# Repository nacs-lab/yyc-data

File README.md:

# License

All source code in this repo is under GPLv3+.

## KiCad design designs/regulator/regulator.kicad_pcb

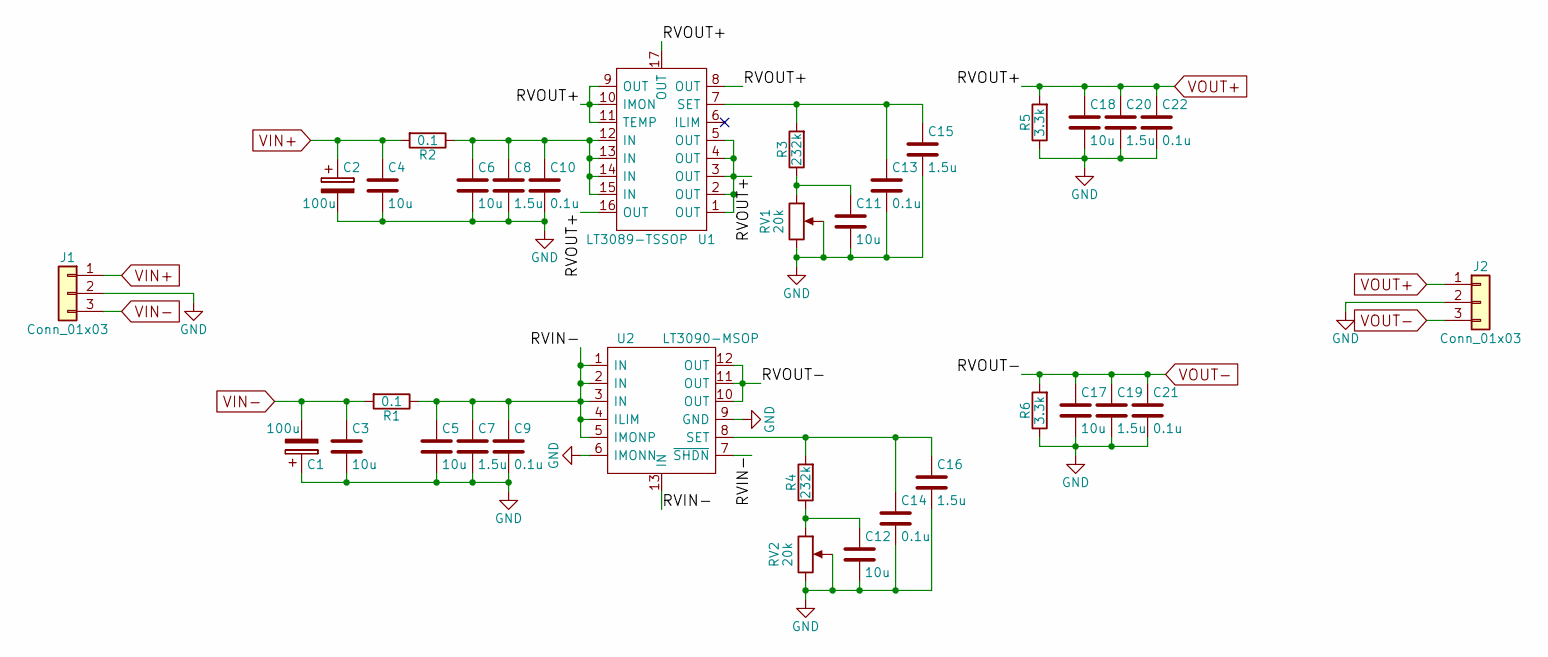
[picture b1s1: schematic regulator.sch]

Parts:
C1, C2: 100u; CP_Radial_D10.0mm_P5.00mm
C3, C4, C5, C6, C11, C12, C17, C18: 10u; C_0603
C7, C8, C15, C16, C19, C20: 1.5u; C_0805
C9, C10, C13, C14, C21, C22: 0.1u; C_0805
J1, J2: Conn_01x03; 3-pins_150mil
R1, R2: 0.1; R_0603
R3, R4: 232k; R_0603
R5, R6: 3.3k; R_0603
RV1, RV2: 20k; Potentiometer_Trimmer_Bourns_3269W
U1: LT3089-TSSOP; TSSOP-16-1EP_4.4x5mm_Pitch0.65mm
U2: LT3090-MSOP; MSOP-12-1EP_3x4mm_Pitch0.65mm

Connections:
/RVIN-: C5.1, C7.1, C9.1, R1.1, U2.1 (IN), U2.2 (IN), U2.3 (IN), U2.4 (ILIM), U2.5 (IMONP), U2.7 (~SHDN), U2.13 (IN)
GND: C1.1, C2.2, C3.2, C4.2, C5.2, C6.2, C7.2, C8.2, C9.2, C10.2, C11.2, C12.2, C13.2, C14.2, C15.2, C16.2, C17.2, C18.2, C19.2, C20.2, C21.2, C22.2, J1.2, J2.2, R5.1, R6.1, RV1.2, RV1.3, RV2.2, RV2.3, U2.6 (IMONN), U2.9 (GND)
unnamed: C6.1, C8.1, C10.1, R2.1, U1.12 (IN), U1.13 (IN), U1.14 (IN), U1.15 (IN)
unnamed: C11.1, R3.1, RV1.1
unnamed: C12.1, R4.1, RV2.1
unnamed: C13.1, C15.1, R3.2, U1.7 (SET)
unnamed: C14.1, C16.1, R4.2, U2.8 (SET)
VIN+: C2.1, C4.1, J1.1, R2.2
VIN-: C1.2, C3.1, J1.3, R1.2
VOUT+: C18.1, C20.1, C22.1, J2.1, R5.2, U1.1 (OUT), U1.2 (OUT), U1.3 (OUT), U1.4 (OUT), U1.5 (OUT), U1.8 (OUT), U1.9 (OUT), U1.10 (IMON), U1.11 (TEMP), U1.16 (OUT), U1.17 (OUT)
VOUT-: C17.1, C19.1, C21.1, J2.3, R6.2, U2.10 (OUT), U2.11 (OUT), U2.12 (OUT)

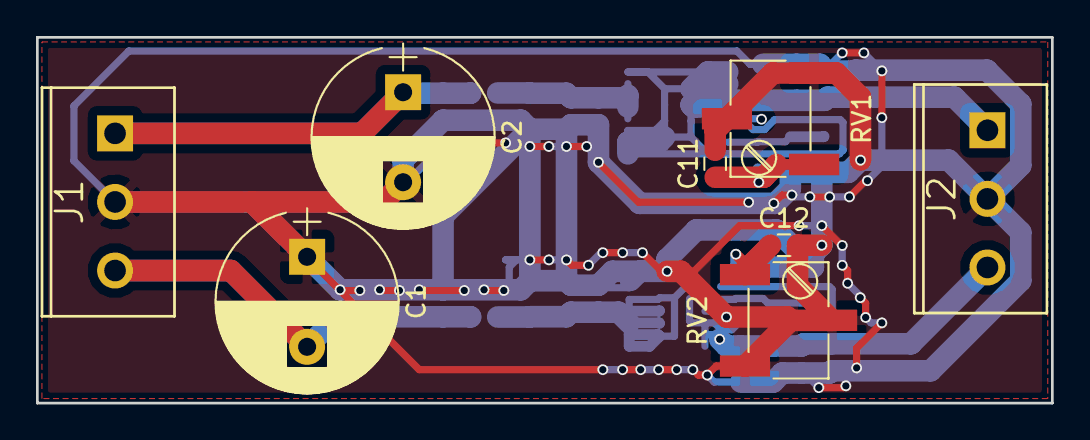
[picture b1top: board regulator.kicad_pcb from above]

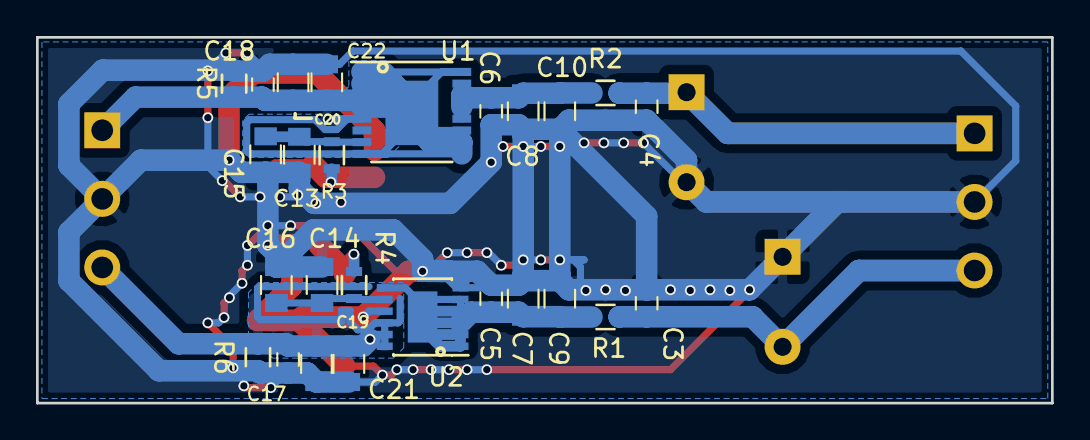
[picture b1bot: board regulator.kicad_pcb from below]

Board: 4 copper layers, 56.4 x 20.3 mm, 34 parts (26 on the bottom side), 11 nets.

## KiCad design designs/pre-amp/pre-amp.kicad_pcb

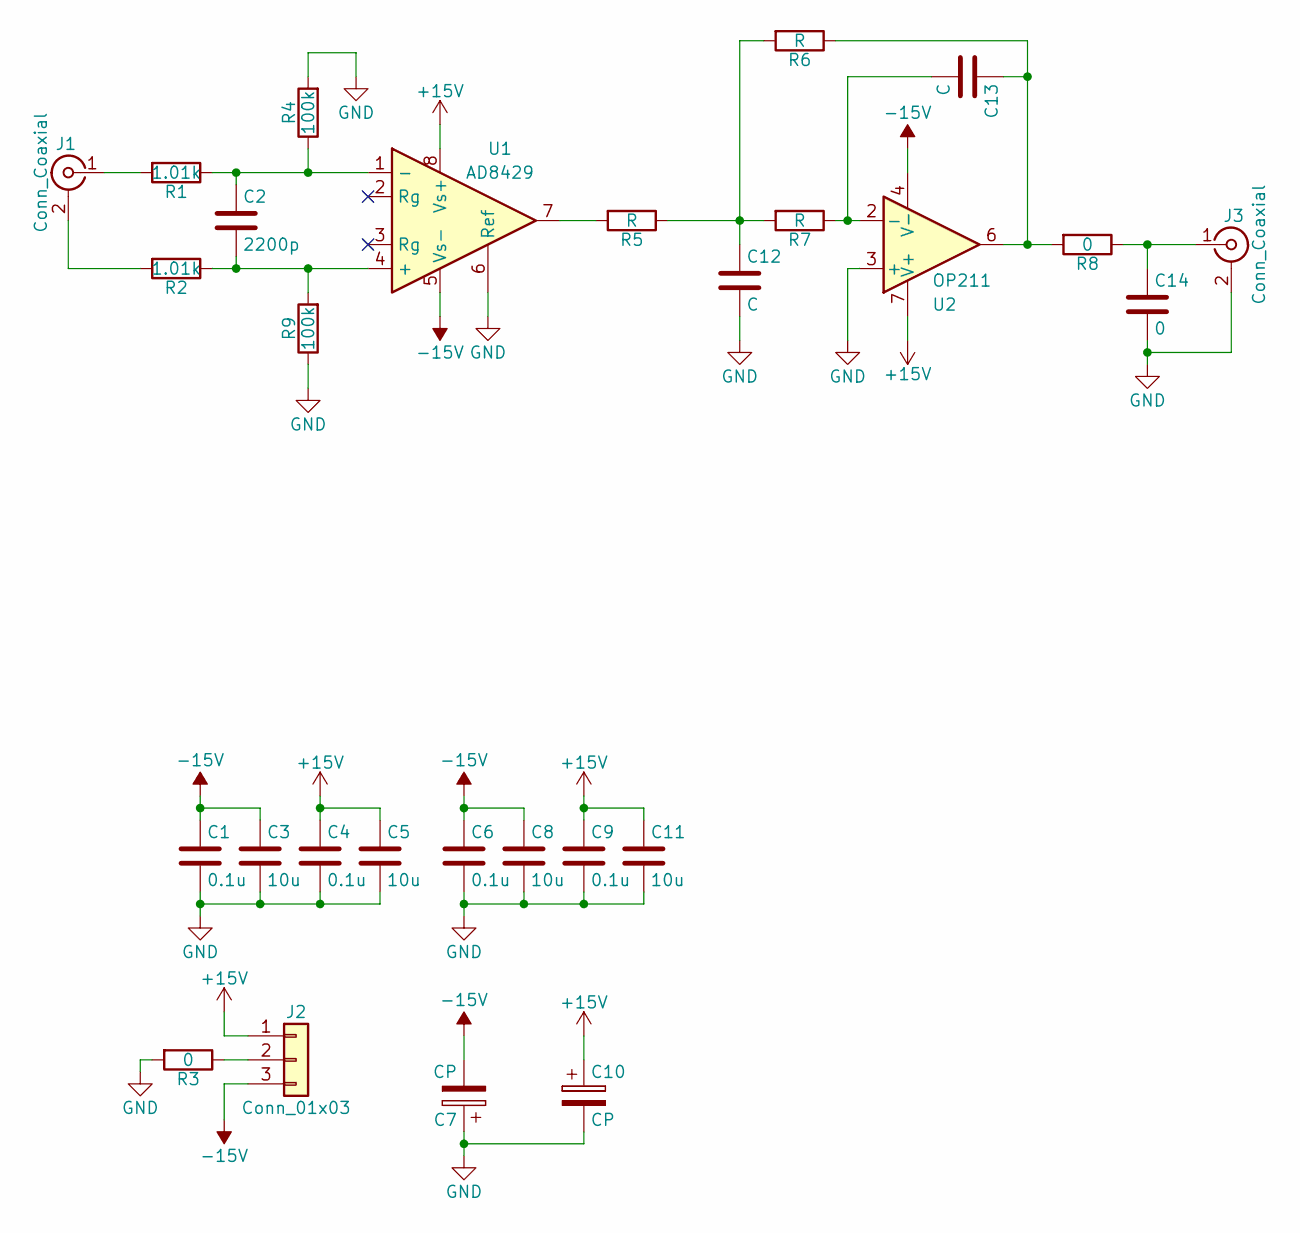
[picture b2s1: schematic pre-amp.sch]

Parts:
C1, C4, C6, C9: 0.1u; C_0603
C2: 2200p; C_0603
C3, C5, C8, C11: 10u; C_0603
C7, C10: CP; CP_Radial_D5.0mm_P2.00mm
C12, C13: C; C_0603
C14: 0; C_0603
J1, J3: Conn_Coaxial; BNC_Socket_Right-Angle_LargePads
J2: Conn_01x03; 3-pins_150mil
R1, R2: 1.01k; R_0603
R3, R8: 0; R_0603
R4, R9: 100k; R_0603
R5, R6, R7: R; R_0603
U1: AD8429; SOIC-8_3.9x4.9mm_Pitch1.27mm
U2: OP211; SOIC-8_3.9x4.9mm_Pitch1.27mm

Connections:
+15V: C4.1, C5.1, C9.1, C10.1, C11.1, J2.1, U1.8 (Vs+), U2.7 (V+)
-15V: C1.1, C3.1, C6.1, C7.2, C8.1, J2.3, U1.5 (Vs-), U2.4 (V-)
GND: C1.2, C3.2, C4.2, C5.2, C6.2, C7.1, C8.2, C9.2, C10.2, C11.2, C12.2, C14.2, J3.2 (Ext), R3.2, R4.2, R9.1, U1.6 (Ref), U2.3 (+)
unnamed: C2.1, R1.1, R4.1, U1.1 (-)
unnamed: C2.2, R2.1, R9.2, U1.4 (+)
unnamed: C12.1, R5.1, R6.2, R7.2
unnamed: C13.1, R6.1, R8.2, U2.6
unnamed: C13.2, R7.1, U2.2 (-)
unnamed: C14.1, J3.1 (In), R8.1
unnamed: J1.1 (In), R1.2
unnamed: J1.2 (Ext), R2.2
unnamed: J2.2, R3.1
unnamed: R5.2, U1.7

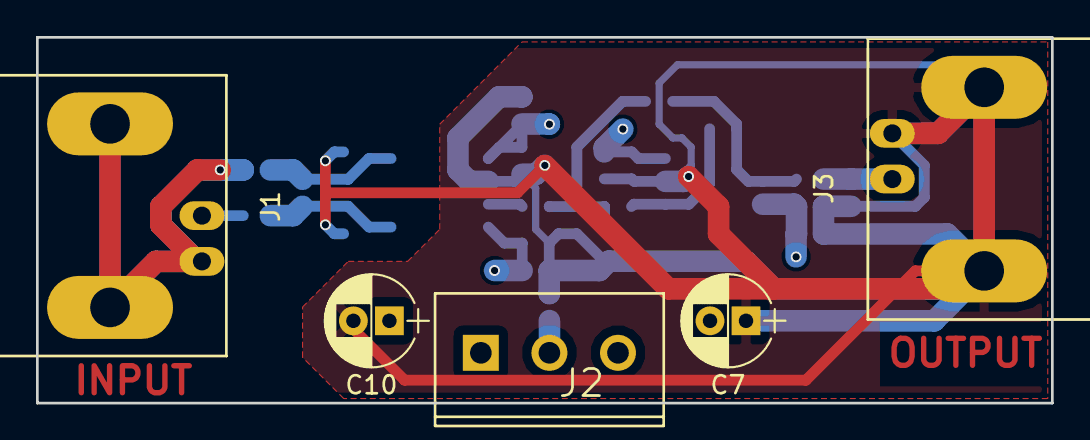
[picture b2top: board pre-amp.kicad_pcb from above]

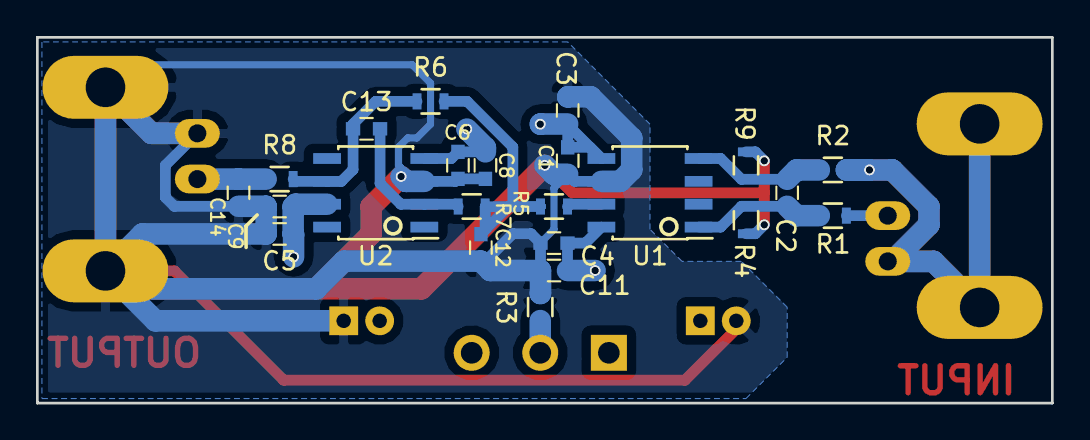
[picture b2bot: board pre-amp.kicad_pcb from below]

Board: 4 copper layers, 56.4 x 20.3 mm, 28 parts (23 on the bottom side), 13 nets.

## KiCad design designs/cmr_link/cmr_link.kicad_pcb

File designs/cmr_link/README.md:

# Orientations

Both connectors (Camera link an the 2x30 connector to the breakout board) and the
decoder chip are on the same (front) side of the board, which is the side that
is closer to the FMC connector and the DDS power supply connectors on the
breakout board. Also the side that is farther from the FPGA board/chip.

When looking from the front side of the board with the 2x30 connector on the
bottom and the camera link connector on the top, the PIN 1 of the 2x30 connector
is on the bottom left of the board and it should be connected to the ground on
the breakout board as well as all other odd number pins on this connector.
Pin 60 of the connector is VCC3V3 from the FPGA board.

# Camera link pin assignments

According to [Andor's document](http://www.andor.com/learning-academy/camera-link-output-ixon-ultra-output-for-direct-data-access), each pixel is a 16bit little endian integer, and according to the standard Port A and Port B should be used in this case.

# Microstrip

Trace width: 10 mil

Trace separation: 6 mil

Trace thickness: 1.7 mil

Dielectric thickness: 11.9 mil

Relative dielectric constant: 4.5

Differential impedance: 100.4 Ohm

# Useful documents

* Sunstone

    [Sunstone capabilities](http://www.sunstone.com/pcb-capabilities/pcb-manufacturing-capabilities)

    [Sunstone board dimensions](http://www.sunstone.com/pcb-products/pcbexpress-quickturn/quickturn-pcb-construction)

* Calculators

    [Microstrip calculator](http://www.multek.se/engelska/engineering/pcb-structures-2/differential-microstrip-impedance-calculator-2)

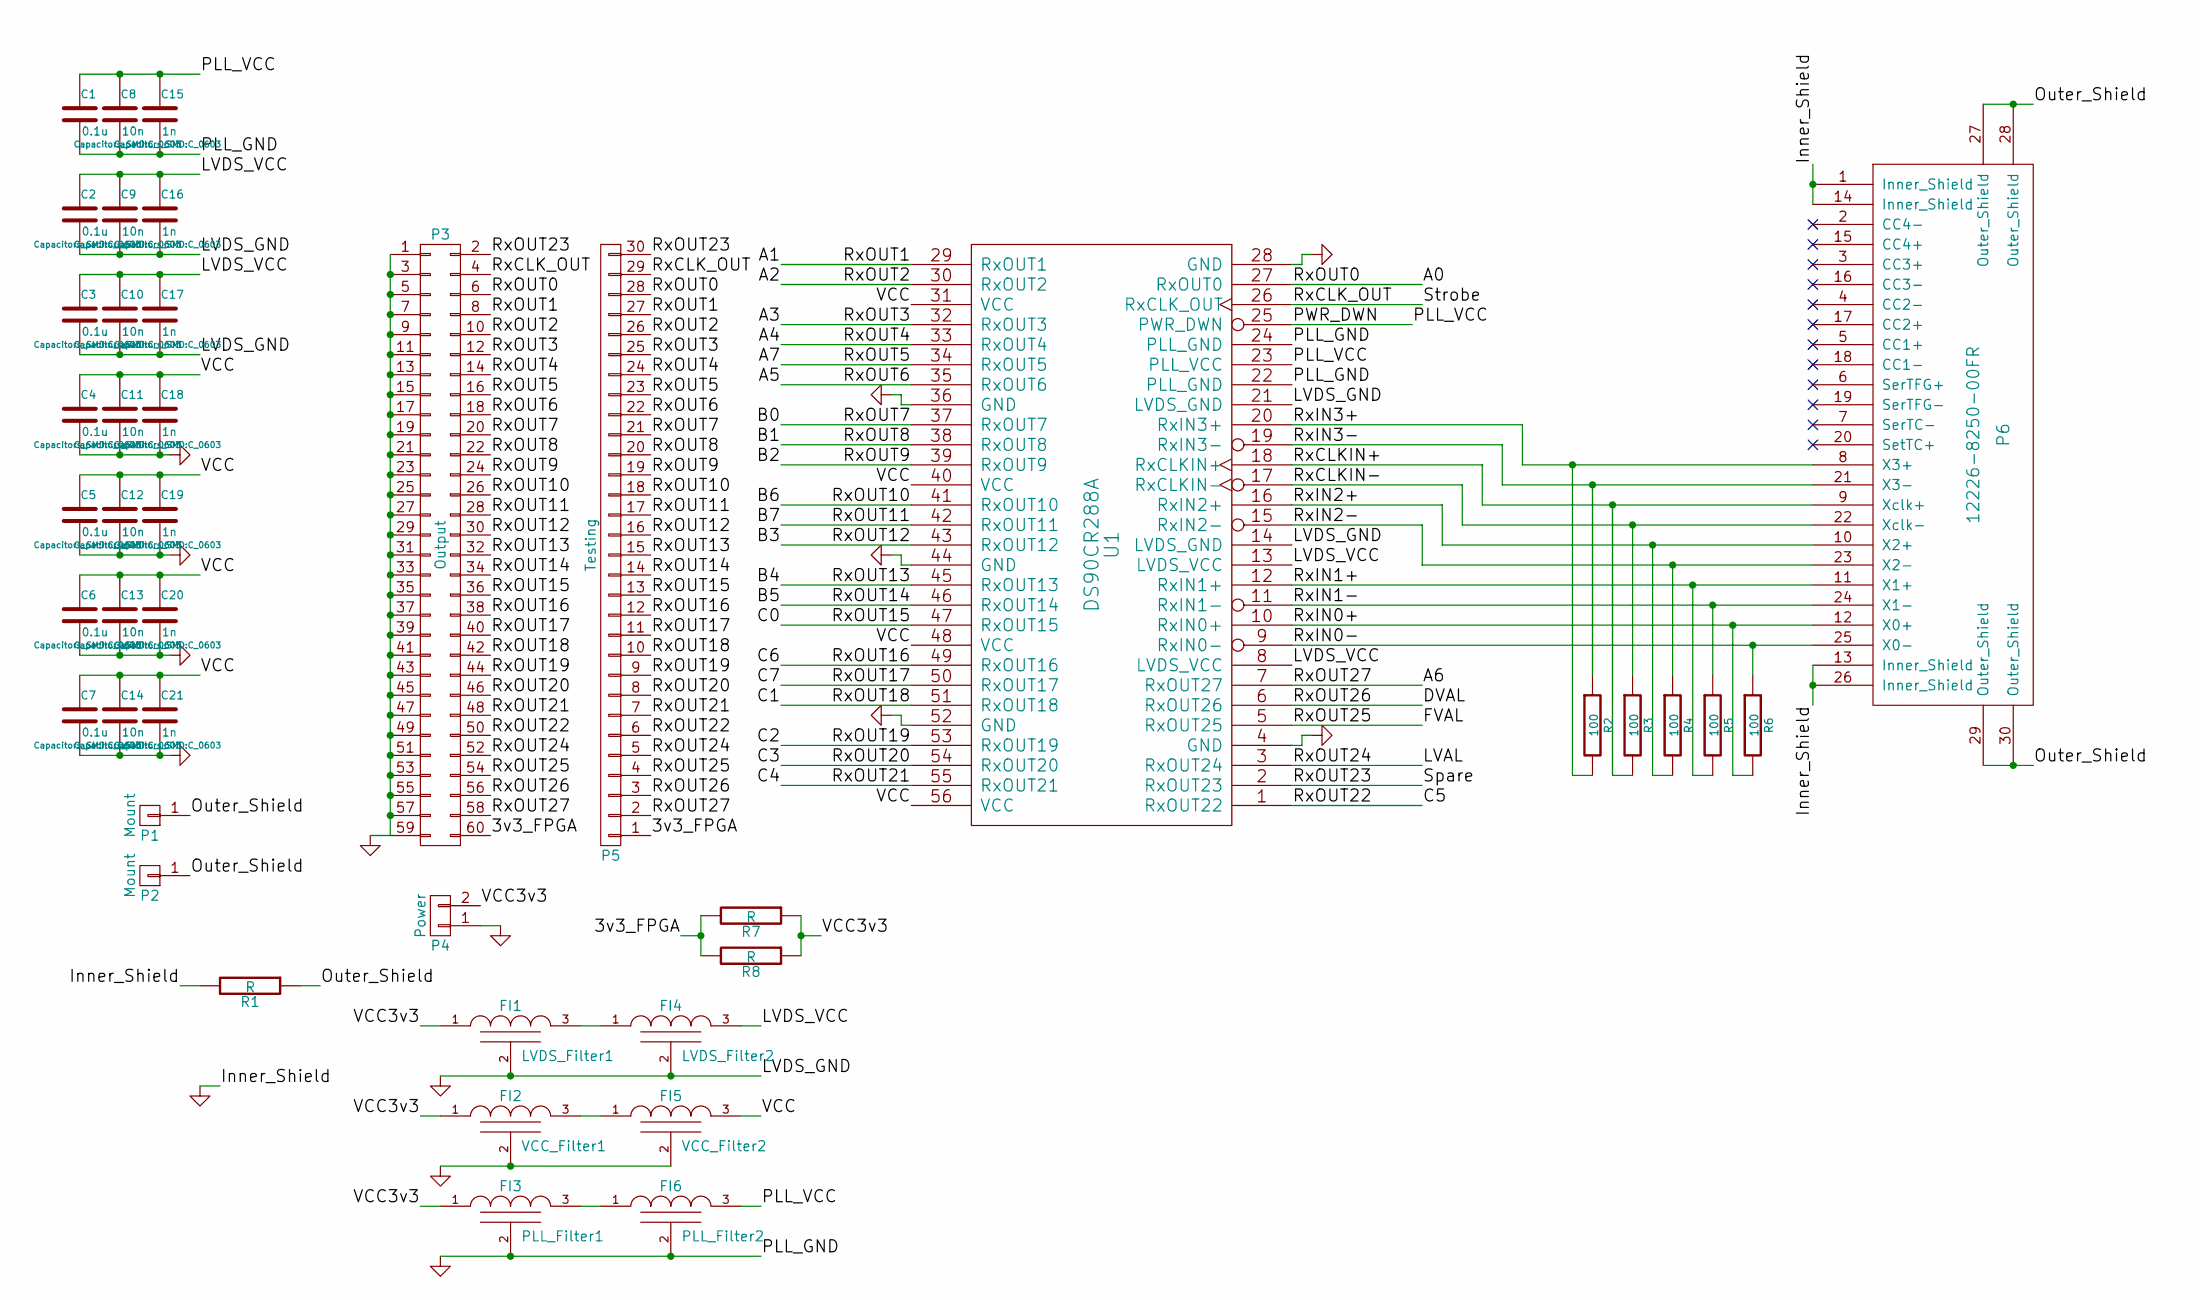
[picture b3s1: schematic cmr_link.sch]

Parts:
C1, C2, C3, C4, C5, C6, C7: 0.1u; C_0603
C8, C9, C10, C11, C12, C13, C14: 10n; C_0603
C15, C16, C17, C18, C19, C20, C21: 1n; C_0603
FI1: LVDS_Filter1; EMI_Filter_1207
FI2: VCC_Filter1; EMI_Filter_1207
FI3: PLL_Filter1; EMI_Filter_1207
FI4: LVDS_Filter2; EMI_Filter_1207
FI5: VCC_Filter2; EMI_Filter_1207
FI6: PLL_Filter2; EMI_Filter_1207
P1, P2: Mount; 1pin
P3: Output; 2x30_2mm
P4: Power; 2-pins_150mil
P5: Testing; 1x30_2mm
P6: 12226-8250-00FR
R1, R7, R8: R; R_0603
R2, R3, R4, R5, R6: 100; R_0603
U1: DS90CR288A; tssop-56-DGG

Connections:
/3v3_FPGA: P3.60, P5.1, R7.2, R8.2
/A0: P3.6, P5.28, U1.27 (RxOUT0)
/A1: P3.8, P5.27, U1.29 (RxOUT1)
/A2: P3.10, P5.26, U1.30 (RxOUT2)
/A3: P3.12, P5.25, U1.32 (RxOUT3)
/A4: P3.14, P5.24, U1.33 (RxOUT4)
/A5: P3.18, P5.22, U1.35 (RxOUT6)
/A6: P3.58, P5.2, U1.7 (RxOUT27)
/A7: P3.16, P5.23, U1.34 (RxOUT5)
/B0: P3.20, P5.21, U1.37 (RxOUT7)
/B1: P3.22, P5.20, U1.38 (RxOUT8)
/B2: P3.24, P5.19, U1.39 (RxOUT9)
/B3: P3.30, P5.16, U1.43 (RxOUT12)
/B4: P3.32, P5.15, U1.45 (RxOUT13)
/B5: P3.34, P5.14, U1.46 (RxOUT14)
/B6: P3.26, P5.18, U1.41 (RxOUT10)
/B7: P3.28, P5.17, U1.42 (RxOUT11)
/C0: P3.36, P5.13, U1.47 (RxOUT15)
/C1: P3.42, P5.10, U1.51 (RxOUT18)
/C2: P3.44, P5.9, U1.53 (RxOUT19)
/C3: P3.46, P5.8, U1.54 (RxOUT20)
/C4: P3.48, P5.7, U1.55 (RxOUT21)
/C5: P3.50, P5.6, U1.1 (RxOUT22)
/C6: P3.38, P5.12, U1.49 (RxOUT16)
/C7: P3.40, P5.11, U1.50 (RxOUT17)
/DVAL: P3.56, P5.3, U1.6 (RxOUT26)
/FVAL: P3.54, P5.4, U1.5 (RxOUT25)
/LVAL: P3.52, P5.5, U1.3 (RxOUT24)
/LVDS_VCC: C2.1, C3.1, C9.1, C10.1, C16.1, C17.1, FI4.3 (VO), U1.8 (LVDS_VCC), U1.13 (LVDS_VCC)
/Outer_Shield: P1.1, P2.1, P6.27 (Outer_Shield), P6.28 (Outer_Shield), P6.29 (Outer_Shield), P6.30 (Outer_Shield), R1.1
/PLL_VCC: C1.1, C8.1, C15.1, FI6.3 (VO), U1.23 (PLL_VCC), U1.25 (PWR_DWN)
/RxCLKIN+: P6.9 (Xclk+), R3.2, U1.18 (RxCLKIN+)
/RxCLKIN-: P6.22 (Xclk-), R3.1, U1.17 (RxCLKIN-)
/RxCLK_OUT: P3.4, P5.29, U1.26 (RxCLK_OUT)
/RxIN0+: P6.12 (X0+), R6.2, U1.10 (RxIN0+)
/RxIN0-: P6.25 (X0-), R6.1, U1.9 (RxIN0-)
/RxIN1+: P6.11 (X1+), R5.2, U1.12 (RxIN1+)
/RxIN1-: P6.24 (X1-), R5.1, U1.11 (RxIN1-)
/RxIN2+: P6.10 (X2+), R4.2, U1.16 (RxIN2+)
/RxIN2-: P6.23 (X2-), R4.1, U1.15 (RxIN2-)
/RxIN3+: P6.8 (X3+), R2.2, U1.20 (RxIN3+)
/RxIN3-: P6.21 (X3-), R2.1, U1.19 (RxIN3-)
/RxOUT23: P3.2, P5.30, U1.2 (RxOUT23)
/VCC: C4.1, C5.1, C6.1, C7.1, C11.1, C12.1, C13.1, C14.1, C18.1, C19.1, C20.1, C21.1, FI5.3 (VO), U1.31 (VCC), U1.40 (VCC), U1.48 (VCC), U1.56 (VCC)
/VCC3v3: FI1.1 (VI), FI2.1 (VI), FI3.1 (VI), P4.2, R7.1, R8.1
GND: C1.2, C2.2, C3.2, C4.2, C5.2, C6.2, C7.2, C8.2, C9.2, C10.2, C11.2, C12.2, C13.2, C14.2, C15.2, C16.2, C17.2, C18.2, C19.2, C20.2, C21.2, FI1.2 (GND), FI2.2 (GND), FI3.2 (GND), FI4.2 (GND), FI5.2 (GND), FI6.2 (GND), P3.1, P3.3, P3.5, P3.7, P3.9, P3.11, P3.13, P3.15, P3.17, P3.19, P3.21, P3.23, P3.25, P3.27, P3.29, P3.31, P3.33, P3.35, P3.37, P3.39, P3.41, P3.43, P3.45, P3.47, P3.49, P3.51, P3.53, P3.55, P3.57, P3.59, P4.1, P6.1 (Inner_Shield), P6.13 (Inner_Shield), P6.14 (Inner_Shield), P6.26 (Inner_Shield), R1.2, U1.4 (GND), U1.14 (LVDS_GND), U1.21 (LVDS_GND), U1.22 (PLL_GND), U1.24 (PLL_GND), U1.28 (GND), U1.36 (GND), U1.44 (GND), U1.52 (GND)
unnamed: FI1.3 (VO), FI4.1 (VI)
unnamed: FI2.3 (VO), FI5.1 (VI)
unnamed: FI3.3 (VO), FI6.1 (VI)

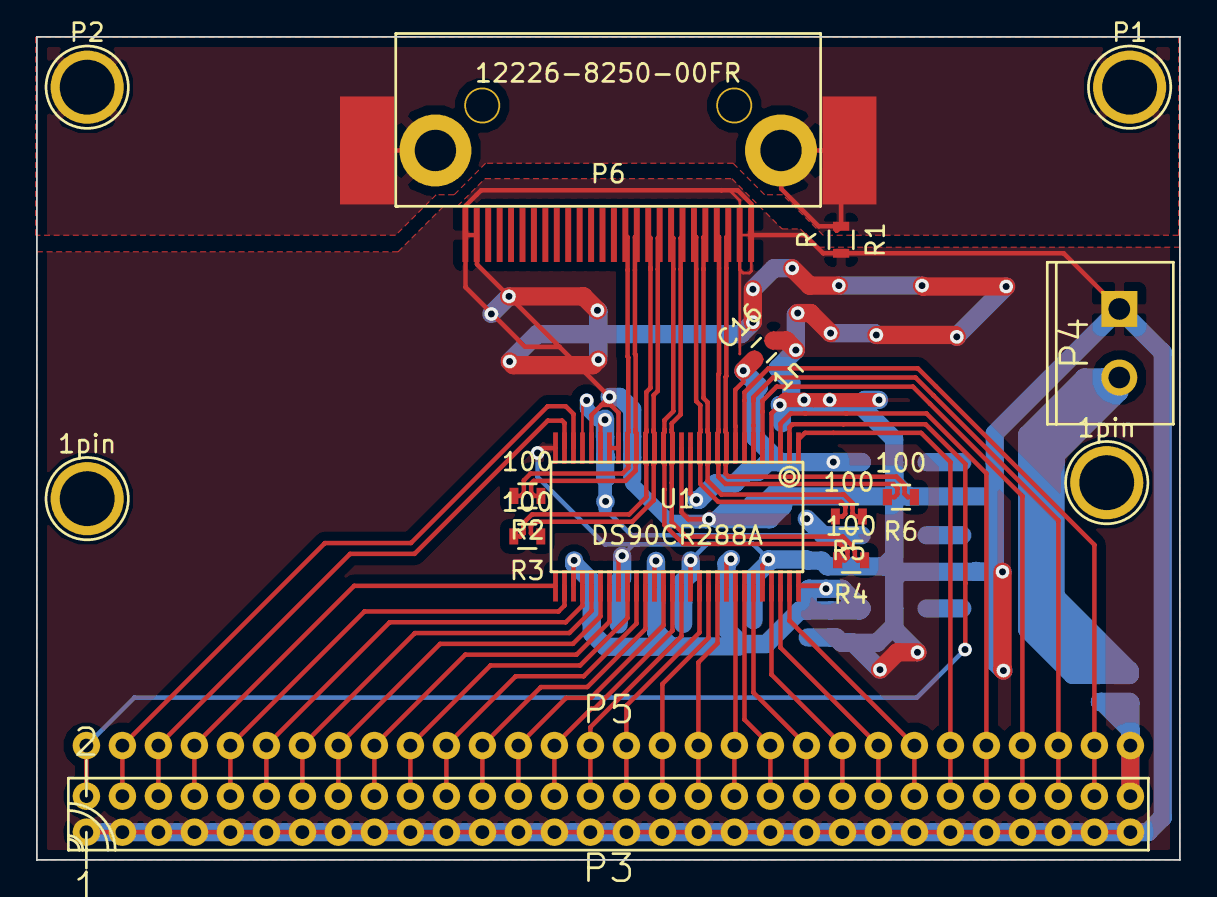
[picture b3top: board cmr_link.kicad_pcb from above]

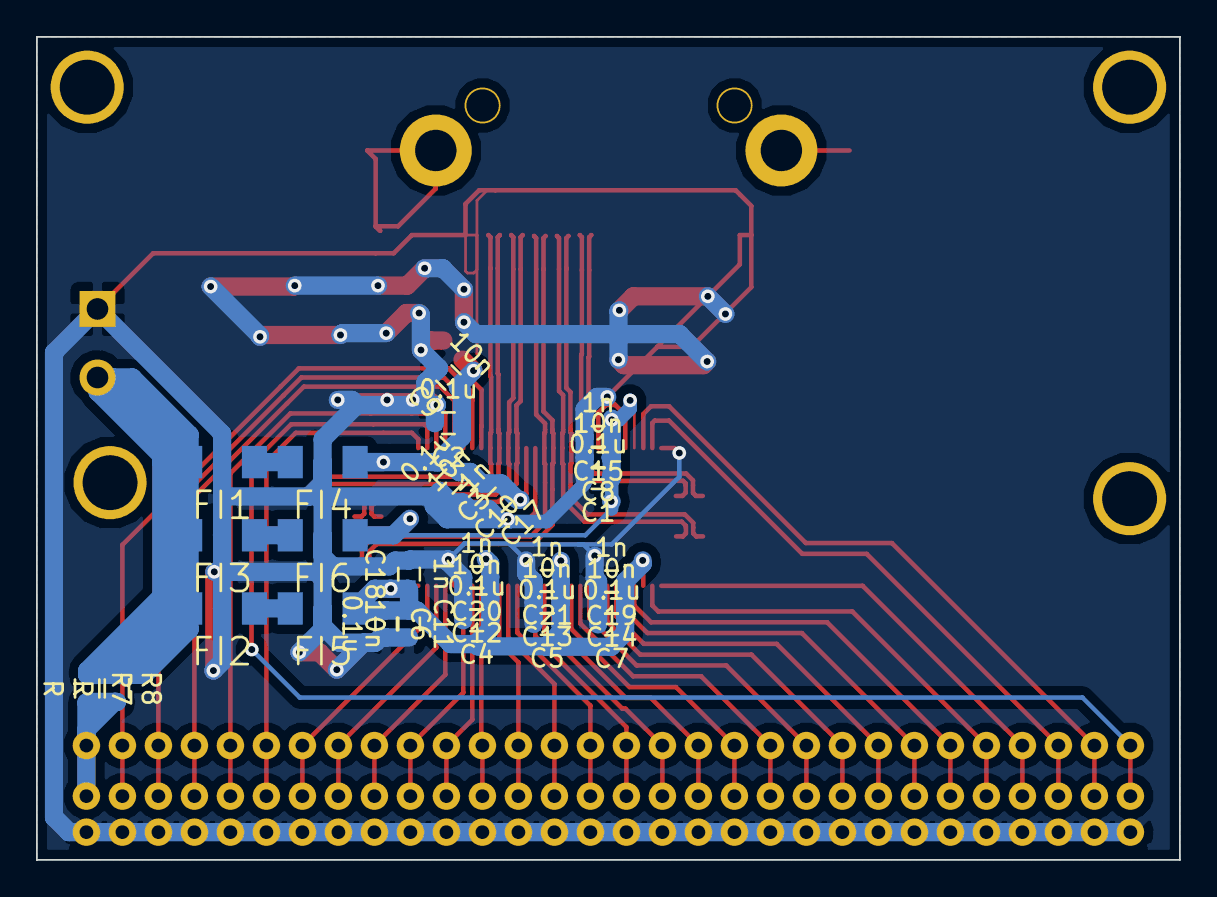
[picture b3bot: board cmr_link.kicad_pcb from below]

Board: 4 copper layers, 63.5 x 45.7 mm, 44 parts (28 on the bottom side), 49 nets.

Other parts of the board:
1pin, 1pin#2: VAL**; 1pin

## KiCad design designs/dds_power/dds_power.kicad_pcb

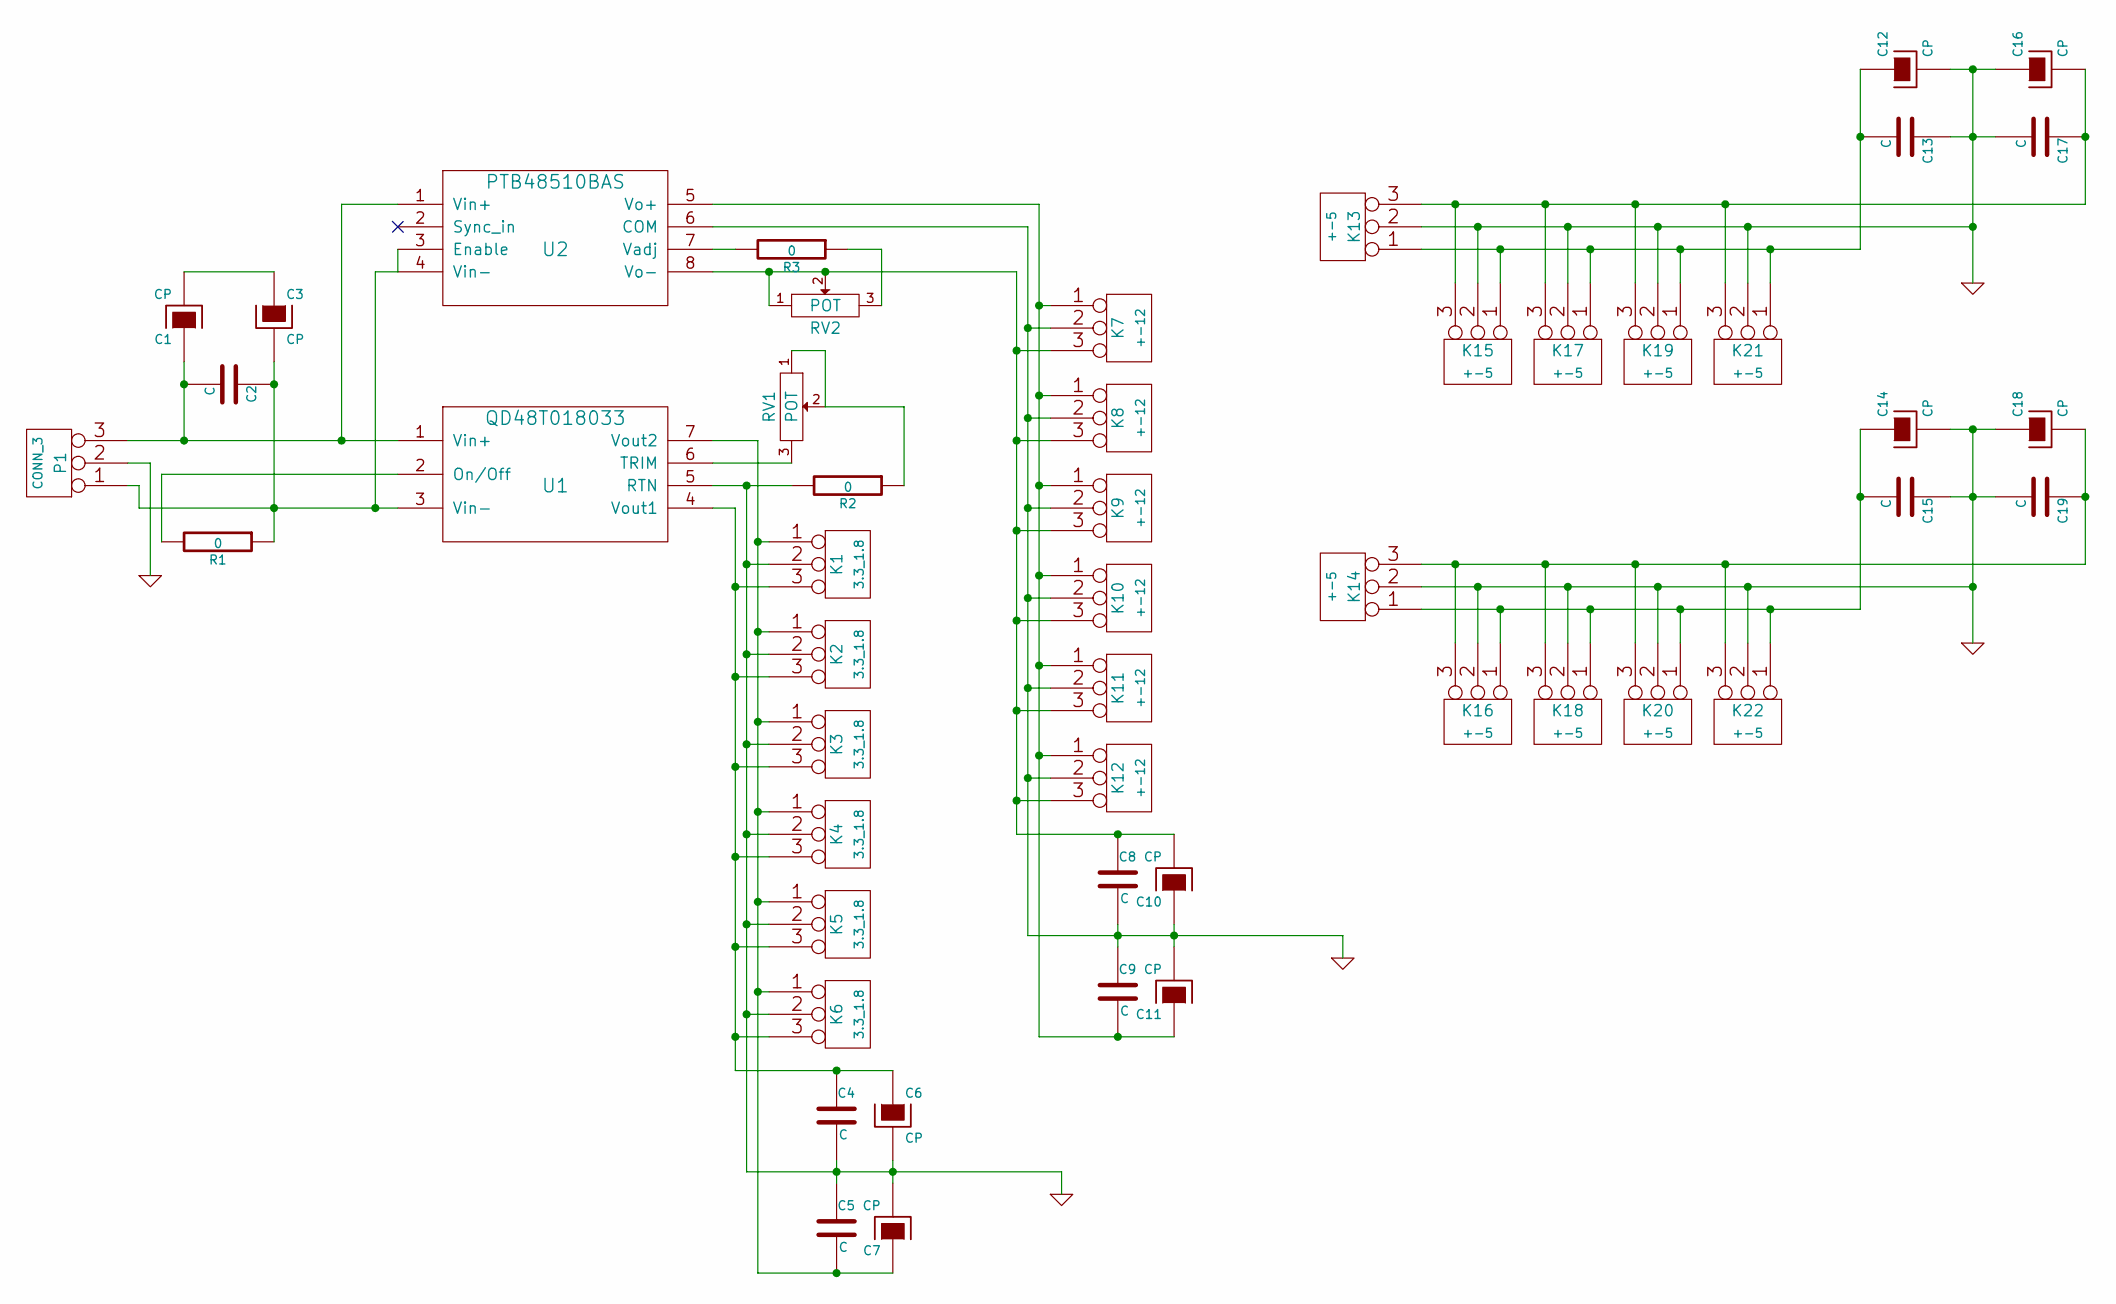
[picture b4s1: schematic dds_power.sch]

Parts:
C1, C3, C6, C7, C10, C11, C12, C14, C16, C18: CP; C_Radial_D5_L11_P2
C2, C4, C5, C8, C9, C13, C15, C17, C19: C; C_1206
K1, K2, K3, K4, K5, K6: 3.3_1.8; 3-pins_150mil
K7, K8, K9, K10, K11, K12: +-12; 3-pins_150mil
K13, K14, K15, K16, K17, K18, K19, K20, K21, K22: +-5; 3-pins_150mil
P1: CONN_3; 3-pins_150mil
R1, R2, R3: 0; R_0603
RV1, RV2: POT; Potentiometer_Bourns_3296Y_3-8Zoll_Angular_ScrewUp
U1: QD48T018033; qd48t018033
U2: PTB48510BAS; ptb48510bas

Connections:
GND: C4.2, C5.1, C6.2, C7.2, C8.2, C9.1, C10.1, C11.2, C12.2, C13.1, C14.2, C15.1, C16.1, C17.2, C18.1, C19.2, K1.2 (PM), K2.2 (PM), K3.2 (PM), K4.2 (PM), K5.2 (PM), K6.2 (PM), K7.2 (PM), K8.2 (PM), K9.2 (PM), K10.2 (PM), K11.2 (PM), K12.2 (PM), K13.2 (PM), K14.2 (PM), K15.2 (PM), K16.2 (PM), K17.2 (PM), K18.2 (PM), K19.2 (PM), K20.2 (PM), K21.2 (PM), K22.2 (PM), P1.2 (PM), R2.2, U1.5 (RTN), U2.6 (COM)
unnamed: C1.1, C2.2, P1.3, U1.1 (Vin+), U2.1 (Vin+)
unnamed: C1.2, C3.1
unnamed: C2.1, C3.2, P1.1, R1.1, U1.3 (Vin-), U2.3 (Enable), U2.4 (Vin-)
unnamed: C4.1, C6.1, K1.3, K2.3, K3.3, K4.3, K5.3, K6.3, U1.4 (Vout1)
unnamed: C5.2, C7.1, K1.1, K2.1, K3.1, K4.1, K5.1, K6.1, U1.7 (Vout2)
unnamed: C8.1, C10.2, K7.3, K8.3, K9.3, K10.3, K11.3, K12.3, RV2.1, RV2.2, U2.8 (Vo-)
unnamed: C9.2, C11.1, K7.1, K8.1, K9.1, K10.1, K11.1, K12.1, U2.5 (Vo+)
unnamed: C12.1, C13.2, K13.1, K15.1, K17.1, K19.1, K21.1
unnamed: C14.1, C15.2, K14.1, K16.1, K18.1, K20.1, K22.1
unnamed: C16.2, C17.1, K13.3, K15.3, K17.3, K19.3, K21.3
unnamed: C18.2, C19.1, K14.3, K16.3, K18.3, K20.3, K22.3
unnamed: R1.2, U1.2 (On/Off)
unnamed: R2.1, RV1.1, RV1.2
unnamed: R3.1, RV2.3
unnamed: R3.2, U2.7 (Vadj)
unnamed: RV1.3, U1.6 (TRIM)

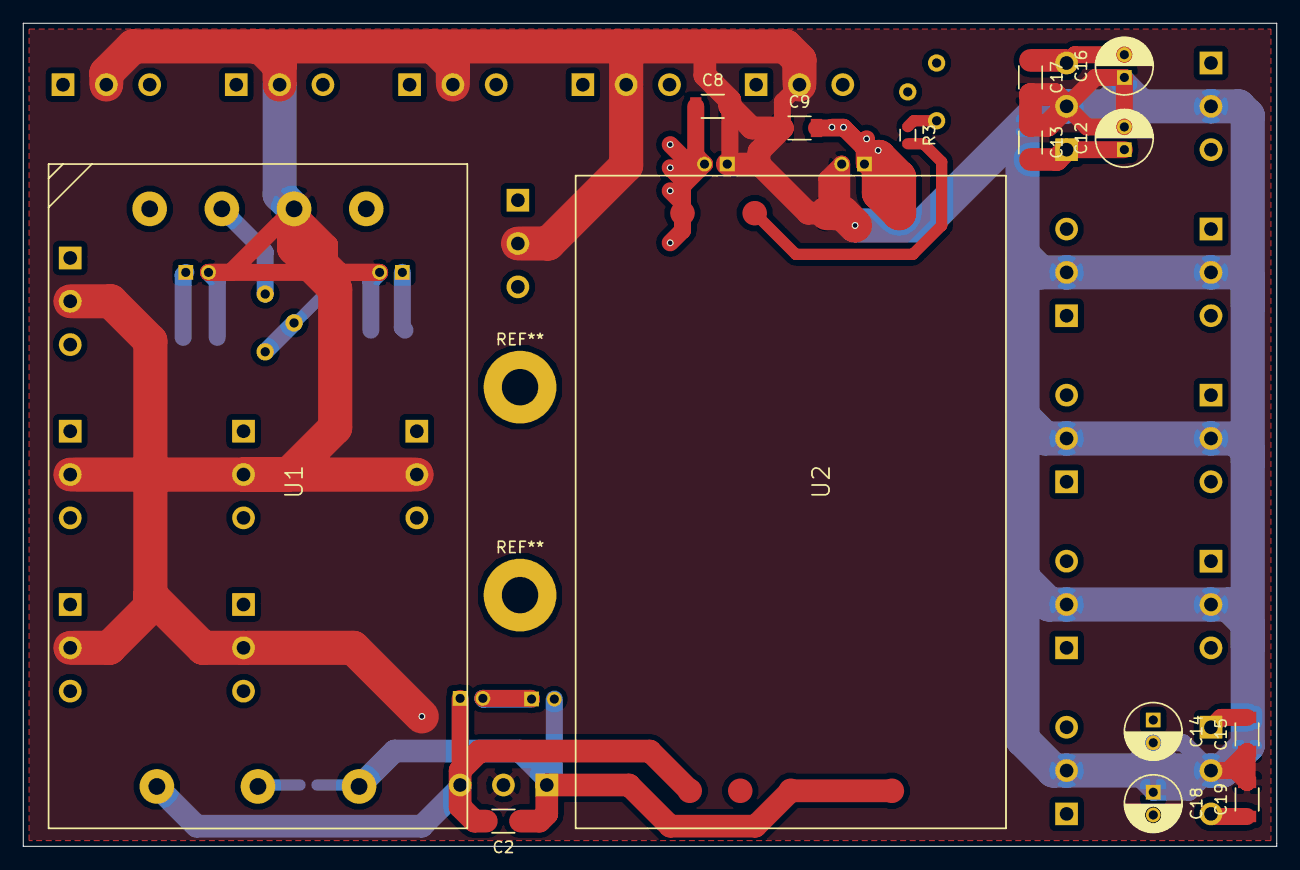
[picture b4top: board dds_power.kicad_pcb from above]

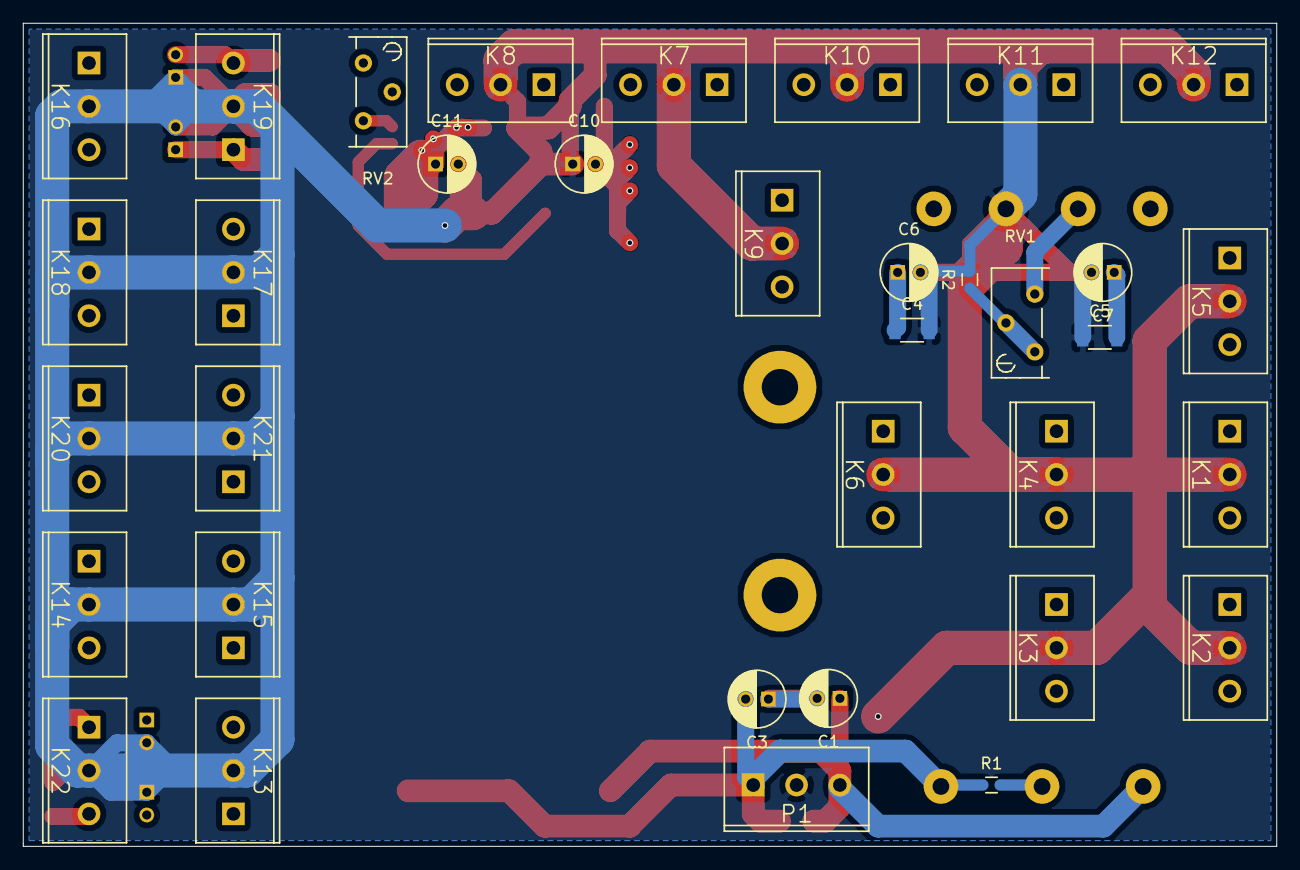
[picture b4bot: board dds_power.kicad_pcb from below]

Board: 4 copper layers, 110.2 x 72.4 mm, 49 parts (35 on the bottom side), 17 nets.
